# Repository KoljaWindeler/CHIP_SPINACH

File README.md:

# CHIP_SPINACH
A DIP that carries 38 WS2812 LEDs. Still requires an LED driver (like the SALSA)

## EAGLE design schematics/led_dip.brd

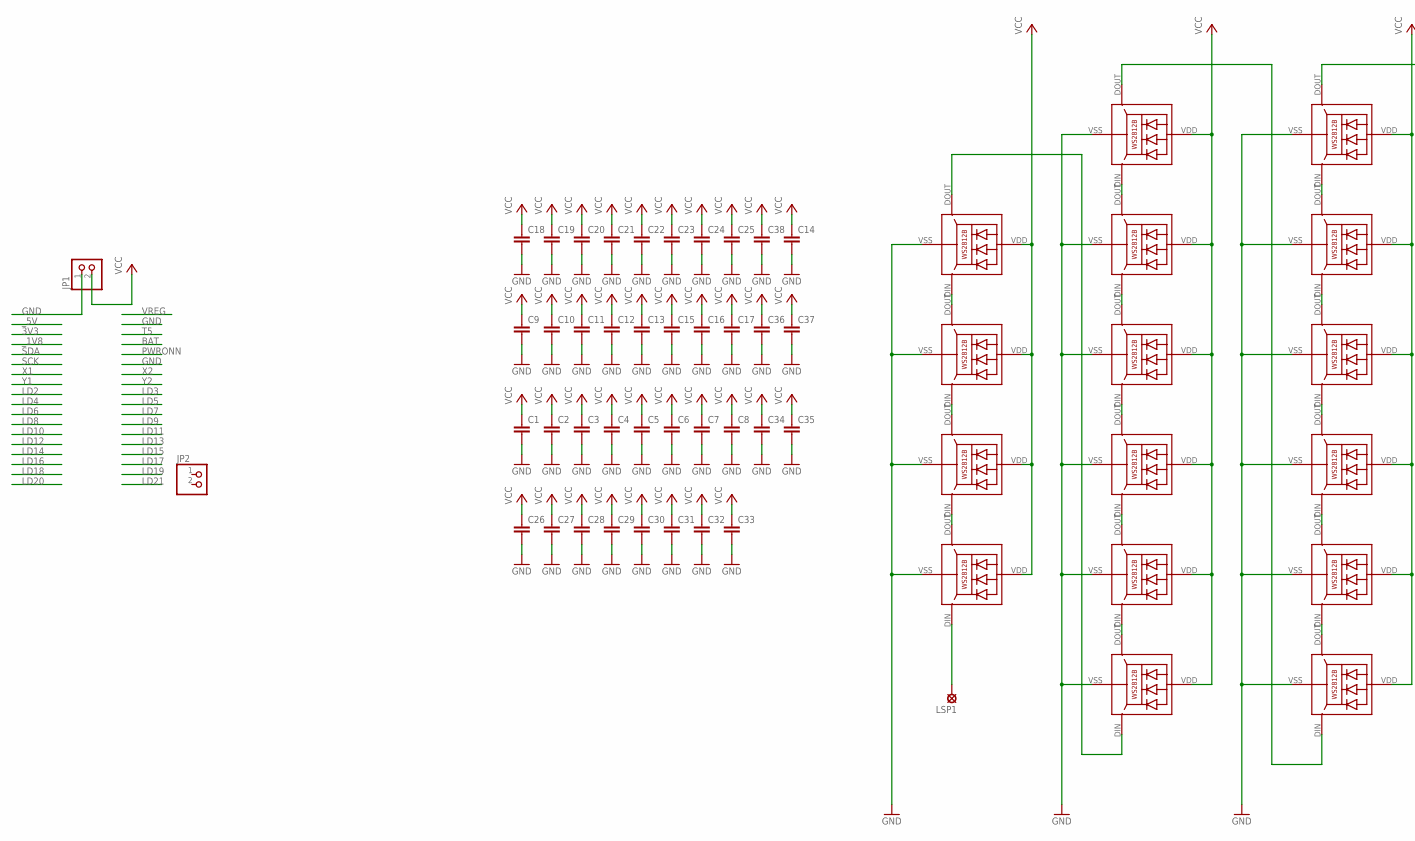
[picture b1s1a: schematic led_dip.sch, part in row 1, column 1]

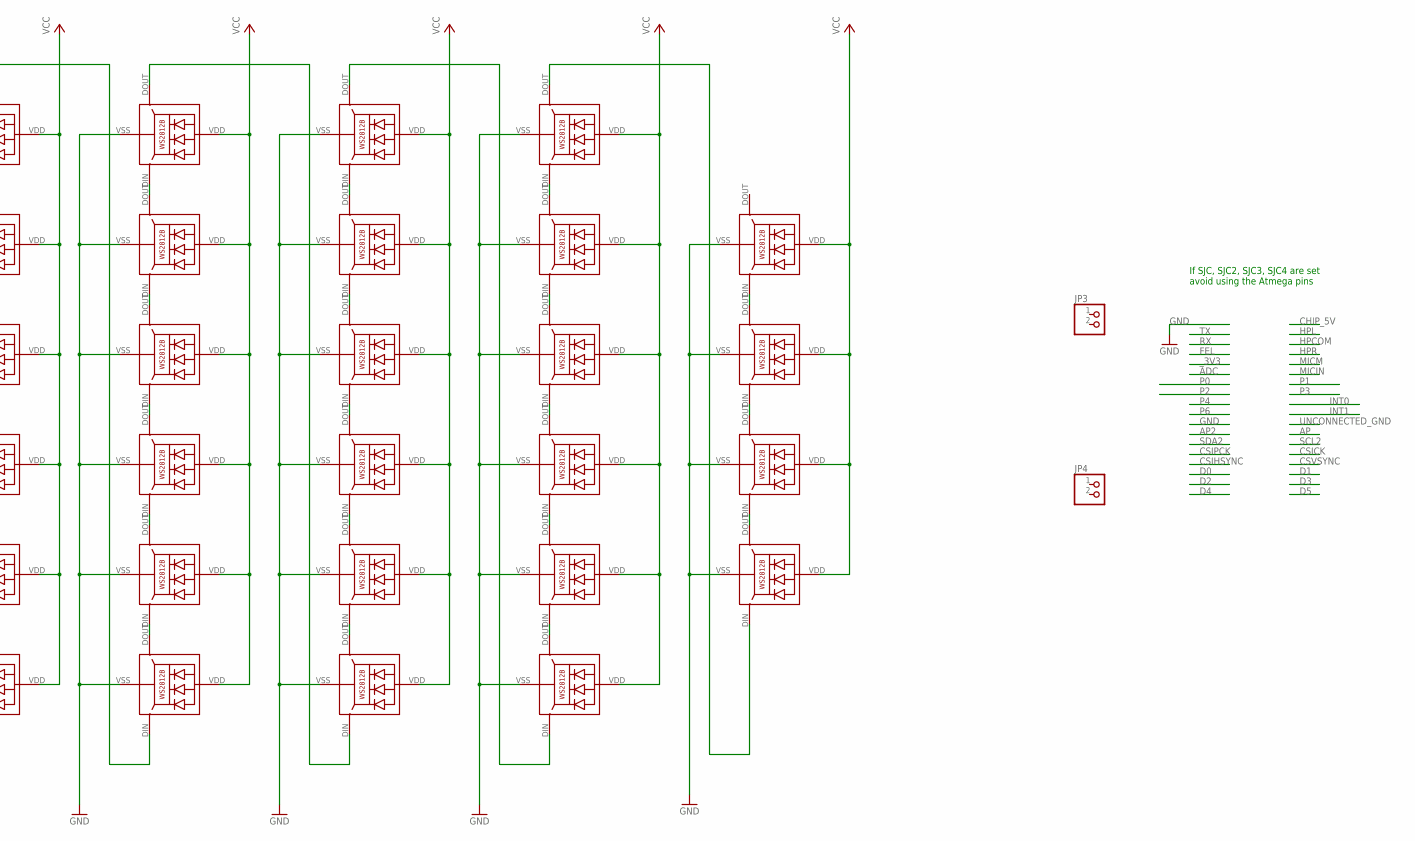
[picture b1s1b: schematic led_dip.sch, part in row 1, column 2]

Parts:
C1, C2, C3, C4, C5, C6, C7, C8, C9, C10, C11, C12, C13, C14, C15, C16, C17, C18, C19, C20, C21, C22, C23, C24, C25, C26, C27, C28, C29, C30, C31, C32, C33, C34, C35, C36, C37, C38: C-EUC0805; C0805
JP1, JP2, JP3, JP4: PINHD-1X2; 1X02
LED1, LED2, LED3, LED4, LED5, LED6, LED7, LED8, LED9, LED10, LED11, LED12, LED13, LED14, LED15, LED16, LED17, LED18, LED19, LED20, LED21, LED22, LED23, LED24, LED25, LED26, LED27, LED28, LED30, LED31, LED32, LED33, LED34, LED35, LED36, LED37, LED38, LED39: WS2812B
LSP1: LSP10

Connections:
GND: C1.2, C2.2, C3.2, C4.2, C5.2, C6.2, C7.2, C8.2, C9.2, C10.2, C11.2, C12.2, C13.2, C14.2, C15.2, C16.2, C17.2, C18.2, C19.2, C20.2, C21.2, C22.2, C23.2, C24.2, C25.2, C26.2, C27.2, C28.2, C29.2, C30.2, C31.2, C32.2, C33.2, C34.2, C35.2, C36.2, C37.2, C38.2, JP1.1, LED1.VSS (GND), LED2.VSS (GND), LED3.VSS (GND), LED4.VSS (GND), LED5.VSS (GND), LED6.VSS (GND), LED7.VSS (GND), LED8.VSS (GND), LED9.VSS (GND), LED10.VSS (GND), LED11.VSS (GND), LED12.VSS (GND), LED13.VSS (GND), LED14.VSS (GND), LED15.VSS (GND), LED16.VSS (GND), LED17.VSS (GND), LED18.VSS (GND), LED19.VSS (GND), LED20.VSS (GND), LED21.VSS (GND), LED22.VSS (GND), LED23.VSS (GND), LED24.VSS (GND), LED25.VSS (GND), LED26.VSS (GND), LED27.VSS (GND), LED28.VSS (GND), LED30.VSS (GND), LED31.VSS (GND), LED32.VSS (GND), LED33.VSS (GND), LED34.VSS (GND), LED35.VSS (GND), LED36.VSS (GND), LED37.VSS (GND), LED38.VSS (GND), LED39.VSS (GND)
unnamed: LED14.DIN (DI), LSP1.MP
unnamed: LED14.DOUT (DO), LED16.DIN (DI)
unnamed: LED16.DOUT (DO), LED20.DIN (DI)
unnamed: LED12.DIN (DI), LED20.DOUT (DO)
unnamed: LED9.DIN (DI), LED12.DOUT (DO)
unnamed: LED6.DIN (DI), LED9.DOUT (DO)
unnamed: LED6.DOUT (DO), LED7.DIN (DI)
unnamed: LED7.DOUT (DO), LED8.DIN (DI)
unnamed: LED8.DOUT (DO), LED18.DIN (DI)
unnamed: LED3.DIN (DI), LED18.DOUT (DO)
unnamed: LED1.DOUT (DO), LED2.DIN (DI)
unnamed: LED2.DOUT (DO), LED28.DIN (DI)
unnamed: LED22.DIN (DI), LED28.DOUT (DO)
unnamed: LED17.DIN (DI), LED22.DOUT (DO)
unnamed: LED17.DOUT (DO), LED27.DIN (DI)
unnamed: LED1.DIN (DI), LED3.DOUT (DO)
unnamed: LED36.DIN (DI), LED37.DOUT (DO)
unnamed: LED34.DIN (DI), LED36.DOUT (DO)
unnamed: LED4.DIN (DI), LED34.DOUT (DO)
unnamed: LED4.DOUT (DO), LED31.DIN (DI)
unnamed: LED30.DIN (DI), LED31.DOUT (DO)
unnamed: LED38.DOUT (DO), LED39.DIN (DI)
unnamed: LED35.DIN (DI), LED39.DOUT (DO)
unnamed: LED5.DIN (DI), LED35.DOUT (DO)
unnamed: LED5.DOUT (DO), LED32.DIN (DI)
unnamed: LED32.DOUT (DO), LED33.DIN (DI)
unnamed: LED13.DIN (DI), LED15.DOUT (DO)
unnamed: LED11.DIN (DI), LED13.DOUT (DO)
unnamed: LED11.DOUT (DO), LED25.DIN (DI)
unnamed: LED10.DIN (DI), LED25.DOUT (DO)
unnamed: LED10.DOUT (DO), LED19.DIN (DI)
unnamed: LED21.DIN (DI), LED26.DOUT (DO)
unnamed: LED21.DOUT (DO), LED23.DIN (DI)
unnamed: LED23.DOUT (DO), LED24.DIN (DI)
unnamed: LED27.DOUT (DO), LED37.DIN (DI)
unnamed: LED30.DOUT (DO), LED38.DIN (DI)
unnamed: LED15.DIN (DI), LED33.DOUT (DO)
unnamed: LED19.DOUT (DO), LED26.DIN (DI)
VCC: C1.1, C2.1, C3.1, C4.1, C5.1, C6.1, C7.1, C8.1, C9.1, C10.1, C11.1, C12.1, C13.1, C14.1, C15.1, C16.1, C17.1, C18.1, C19.1, C20.1, C21.1, C22.1, C23.1, C24.1, C25.1, C26.1, C27.1, C28.1, C29.1, C30.1, C31.1, C32.1, C33.1, C34.1, C35.1, C36.1, C37.1, C38.1, JP1.2, LED1.VDD, LED2.VDD, LED3.VDD, LED4.VDD, LED5.VDD, LED6.VDD, LED7.VDD, LED8.VDD, LED9.VDD, LED10.VDD, LED11.VDD, LED12.VDD, LED13.VDD, LED14.VDD, LED15.VDD, LED16.VDD, LED17.VDD, LED18.VDD, LED19.VDD, LED20.VDD, LED21.VDD, LED22.VDD, LED23.VDD, LED24.VDD, LED25.VDD, LED26.VDD, LED27.VDD, LED28.VDD, LED30.VDD, LED31.VDD, LED32.VDD, LED33.VDD, LED34.VDD, LED35.VDD, LED36.VDD, LED37.VDD, LED38.VDD, LED39.VDD

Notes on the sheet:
If SJC, SJC2, SJC3, SJC4 are set avoid using the Atmega pins

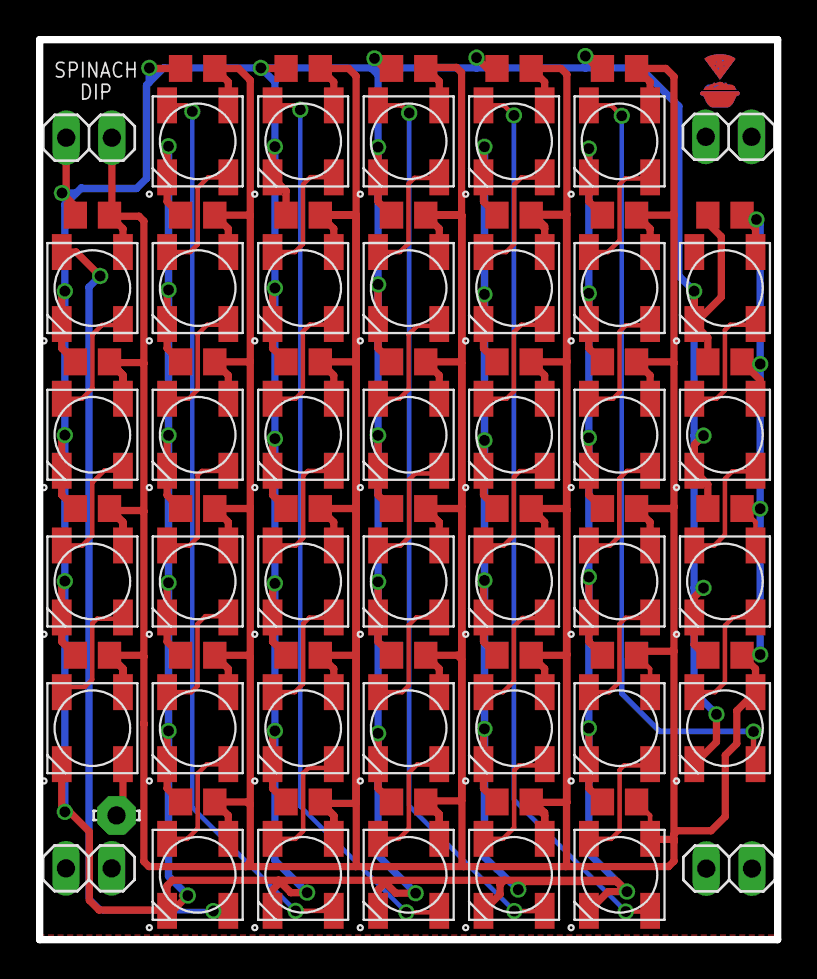
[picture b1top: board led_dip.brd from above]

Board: 2 copper layers, 41.0 x 50.0 mm, 83 parts (1 on the bottom side), 40 nets.

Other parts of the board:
U$2, U$5: LOGO

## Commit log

2016-03-27 init
2016-04-04 added projects dir
2016-04-04 rm projects
2016-04-04 rebased projects
2016-04-04 rem comment
2016-04-04 glow reminder
2016-04-10 added date and screen startup script
2016-04-12 added number display
2016-04-21 added weather init version
2016-08-31 added desc
